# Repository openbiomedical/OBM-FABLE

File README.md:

# OBM-FABLE
FABLE is an electromechanical hand. Through the acquisition of signals generated by the muscles myoelectric contraction next to the elbow, it determines precise finger movements. Electronics is the hub of the system and it is compact, lowcost, completely reengineered to provide a project everywhere reproducible and technologically advanced. This hand is not a prosthesis, it is intended as a development kit. This work is licensed under the Creative Commons Attribution-NonCommercial-ShareAlike 4.0 International License. To view a copy of this license, visit https://creativecommons.org/licenses/by-nc-sa/4.0/legalcode

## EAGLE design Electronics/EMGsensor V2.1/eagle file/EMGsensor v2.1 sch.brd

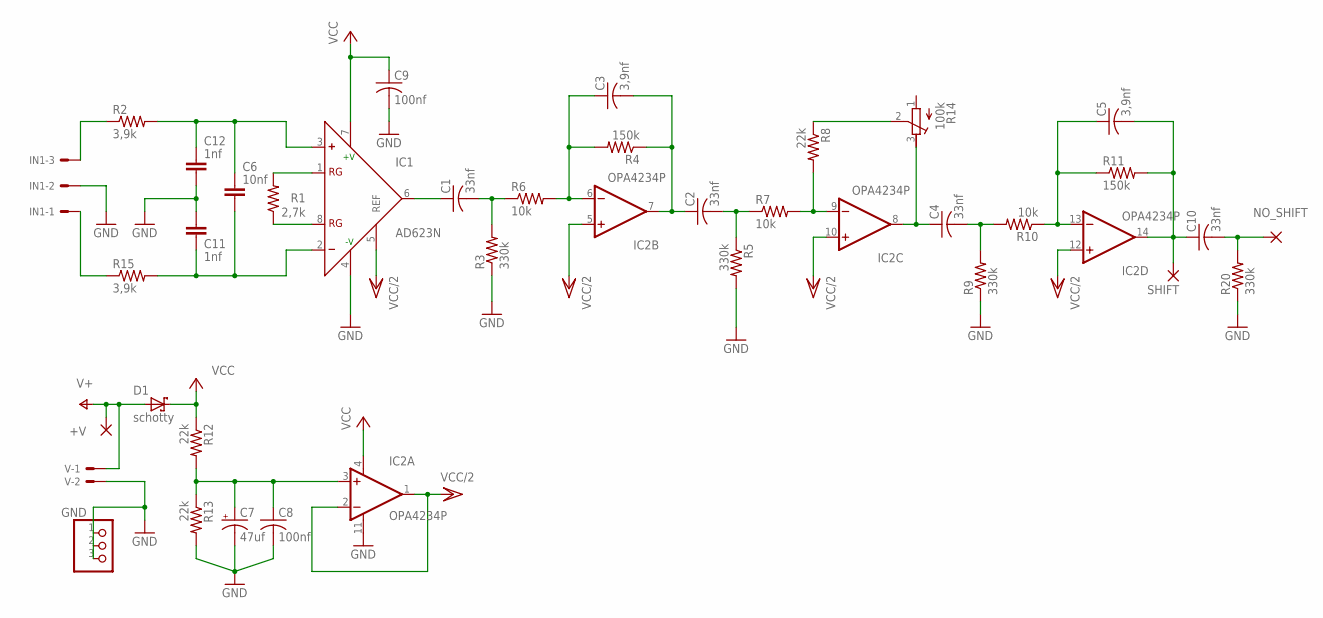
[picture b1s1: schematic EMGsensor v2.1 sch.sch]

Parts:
+V: 2,54/0,9
C1, C2, C10: 33nf; C050-024X044
C3, C5: 3,9nf; C025-025X050
C4: 33nf; C025-025X050
C6: 10nf; C050-024X044
C7: 47uf; E2,5-5
C8, C9: 100nf; C050-024X044
C11, C12: 1nf; C050-024X044
D1: schotty; DO35-7
GND: PINHD-1X3; 1X03
IC1: AD623N; DIL08
IC2: OPA4234P; DIL14
IN1: 22-27-2031-03; 6410-03
NO_SHIFT: 2,54/0,9
R1: 2,7k; 0207/7
R2, R15: 3,9k; 0207/7
R3, R5, R9, R20: 330k; 0207/7
R4: 150k; 0207/5V
R6, R7, R10: 10k; 0207/7
R8, R12, R13: 22k; 0207/7
R11: 150k; 0207/2V
R14: 100k; RTRIM3339P
SHIFT: 2,54/0,9
V: 22-27-2021-02; 6410-02

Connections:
unnamed: C1.1, IC1.6 (OUT)
unnamed: C1.2, R3.2, R6.1
unnamed: C3.1, IC2.6 (-IN), R4.2, R6.2
unnamed: C2.1, C3.2, IC2.7 (OUT), R4.1
unnamed: C2.2, R5.1, R7.1
unnamed: IC2.9 (-IN), R7.2, R8.2
unnamed: C4.1, IC2.8 (OUT), R14.3 (E)
unnamed: C4.2, R9.2, R10.2
unnamed: C5.1, IC2.13 (-IN), R10.1, R11.1
unnamed: C5.2, C10.1, IC2.14 (OUT), R11.2, SHIFT.1
unnamed: R8.1, R14.2 (S)
unnamed: IC1.1 (RG), R1.2
unnamed: C6.1, C12.1, IC1.3 (+), R2.2
unnamed: C6.2, C11.2, IC1.2 (-), R15.2
unnamed: IN1.3, R2.1
unnamed: C10.2, NO_SHIFT.1, R20.2
unnamed: IN1.1, R15.1
unnamed: IC1.5 (REF), IC2.1 (OUT), IC2.2 (-IN)
unnamed: C9.1, D1.C, IC1.7 (+V), IC2.4 (V+), R12.1
unnamed: C7.+, C8.1, IC2.3 (+IN), R12.2, R13.1
unnamed: +V.1, D1.A, V.1
unnamed: IC1.8 (RG), R1.1
unnamed: C7.-, C8.2, C9.2, C11.1, C12.2, GND.1, GND.2, GND.3, IC1.4 (-V), IC2.11 (V-), IN1.2, R3.1, R5.2, R9.1, R13.2, R20.1, V.2
VCC/2: IC2.5 (+IN), IC2.10 (+IN), IC2.12 (+IN)

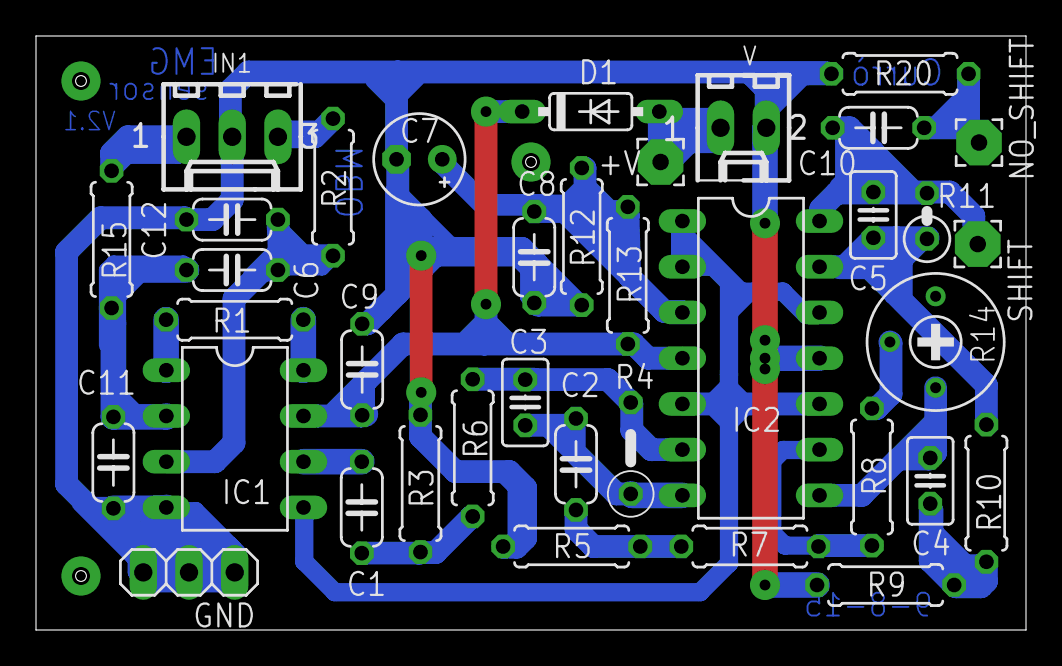
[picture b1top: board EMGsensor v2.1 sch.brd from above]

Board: 2 copper layers, 55.0 x 33.0 mm, 37 parts (0 on the bottom side), 24 nets.

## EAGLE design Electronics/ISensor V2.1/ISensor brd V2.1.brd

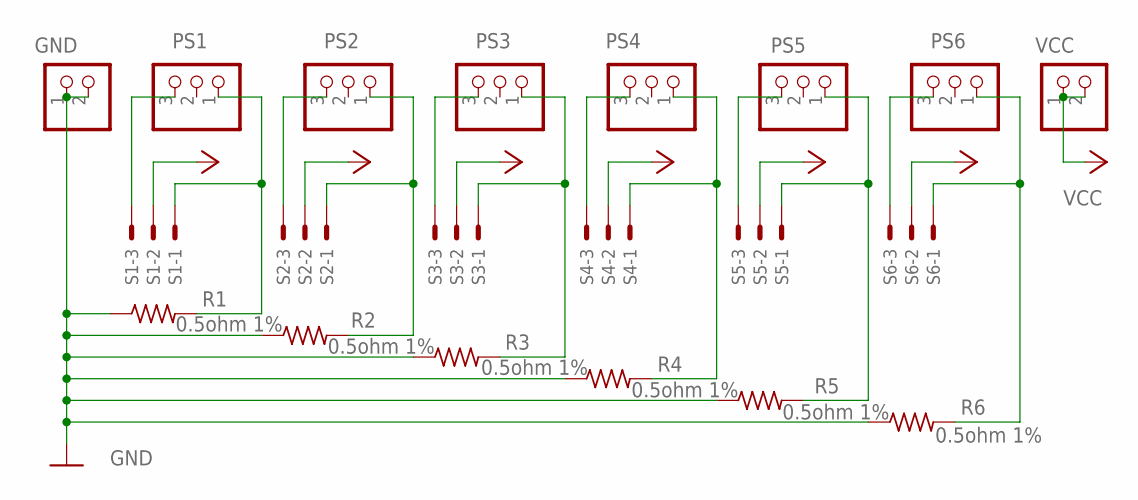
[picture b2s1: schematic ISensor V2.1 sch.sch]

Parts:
GND: PINHD-1X2; 1X02
PS1, PS2, PS3, PS4, PS5, PS6: PINHD-1X3; 1X03
R1, R2, R3, R4, R5, R6: 0.5ohm 1%; R2512
S1, S2, S3, S4, S5, S6: 22-27-2031-03; 6410-03
VCC: PINHD-1X2; 1X02

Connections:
unnamed: PS1.3, S1.3
unnamed: PS1.1, R1.2, S1.1
unnamed: PS2.1, R2.2, S2.1
unnamed: PS3.3, S3.3
unnamed: PS3.1, R3.2, S3.1
unnamed: PS4.3, S4.3
unnamed: PS4.1, R4.2, S4.1
unnamed: PS5.3, S5.3
unnamed: PS5.1, R5.2, S5.1
unnamed: PS6.3, S6.3
unnamed: PS6.1, R6.2, S6.1
unnamed: GND.1, GND.2, R1.1, R2.1, R3.1, R4.1, R5.1, R6.1
PS2: PS2.3, S2.3
VCC: S1.2, S2.2, S3.2, S4.2, S5.2, S6.2, VCC.1, VCC.2

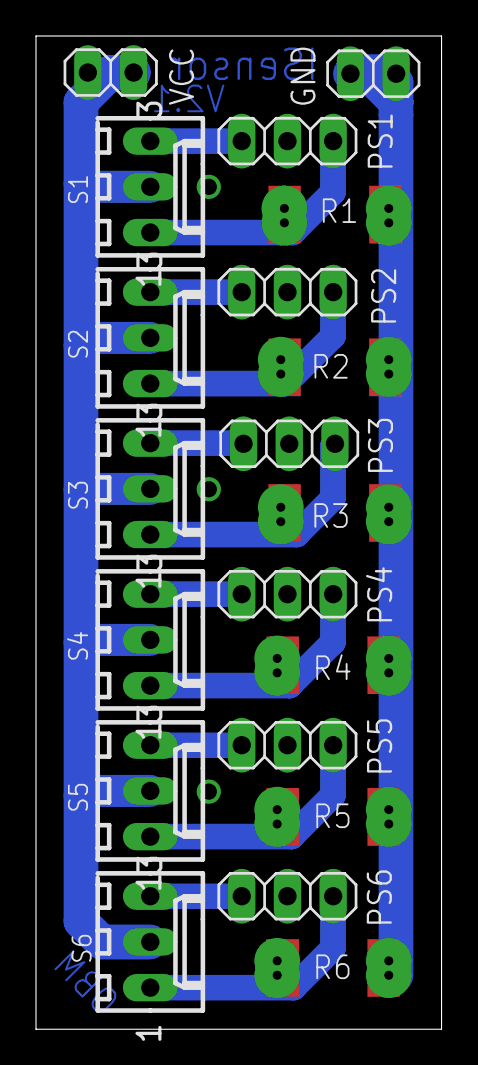
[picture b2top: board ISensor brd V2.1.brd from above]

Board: 2 copper layers, 22.5 x 55.2 mm, 20 parts (0 on the bottom side), 14 nets.

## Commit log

2017-02-14 Rename 3D Model/FABLE V0.2 August 2015/readme to 3D Model/V0.2_FABLE _August2015/readme
